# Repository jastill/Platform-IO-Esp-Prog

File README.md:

# PlatformIO ESP32 Debugging

##Platform IO ESP32 Debug Breakout Board

## PCB from [Osh Park](https://oshpark.com)

## Board

Board: [Adafruit Feather 32](https://www.adafruit.com/product/3405)

ESP [Prog Board](https://github.com/espressif/esp-iot-solution/blob/master/documents/evaluation_boards/ESP-Prog_guide_en.md)

## Misc

Step that got ESP-PROG to connect:

Bizarrely it seemed that loading and then unloading these drivers are the change that caused it to work.

https://www.ftdichip.com/Drivers/VCP.htm
sudo kextunload /Library/Extensions/FTDIUSBSerialDriver.kext

### Helpful links to get the port connected

https://docs.platformio.org/en/latest/plus/debug-tools/esp-prog.html

https://community.platformio.org/t/esp-prog-debugging-on-a-mac-no-device-found/14658

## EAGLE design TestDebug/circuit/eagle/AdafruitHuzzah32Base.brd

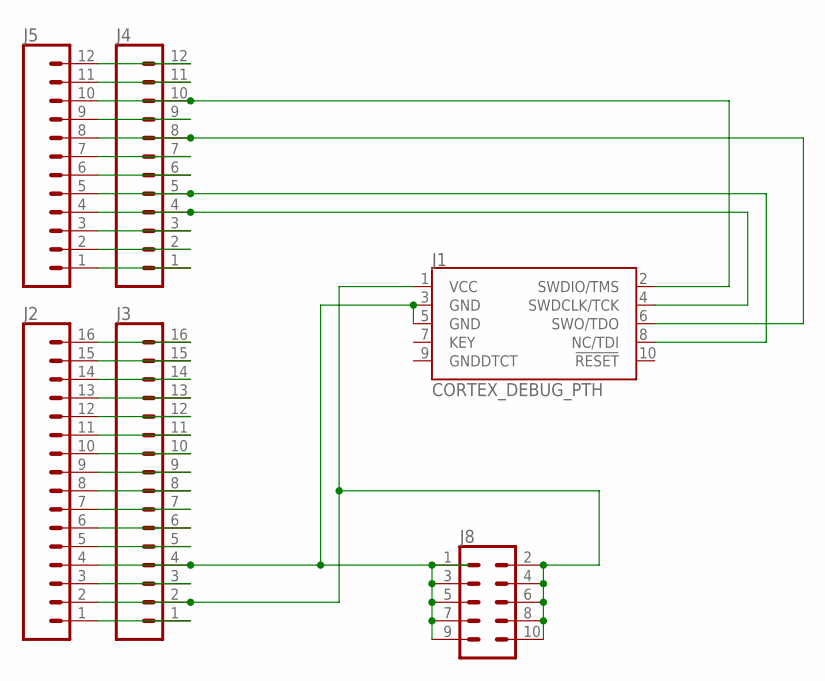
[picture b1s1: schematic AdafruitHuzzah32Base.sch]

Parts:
J1: CORTEX_DEBUG_PTH; 2X5-PTH-1.27MM
J2, J3: CONN_16; 1X16
J4, J5: CONN_12; 1X12
J8: CONN_05X2PTH; 2X5

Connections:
unnamed: J1.1 (VCC), J2.2, J3.2, J8.2, J8.4, J8.6, J8.8, J8.10
unnamed: J1.3 (GND), J1.5 (GND), J2.4, J3.4, J8.1, J8.3, J8.5, J8.7, J8.9
unnamed: J1.6 (SWO/TDO), J4.8, J5.8
unnamed: J1.8 (NC/TDI), J4.5, J5.5
unnamed: J1.4 (SWDCLK/TCK), J4.4, J5.4
unnamed: J1.2 (SWDIO/TMS), J4.10, J5.10
unnamed: J4.12, J5.12
unnamed: J4.11, J5.11
unnamed: J4.9, J5.9
unnamed: J4.7, J5.7
unnamed: J4.6, J5.6
unnamed: J4.3, J5.3
unnamed: J4.2, J5.2
unnamed: J4.1, J5.1
unnamed: J2.16, J3.16
unnamed: J2.15, J3.15
unnamed: J2.14, J3.14
unnamed: J2.13, J3.13
unnamed: J2.12, J3.12
unnamed: J2.11, J3.11
unnamed: J2.10, J3.10
unnamed: J2.9, J3.9
unnamed: J2.8, J3.8
unnamed: J2.7, J3.7
unnamed: J2.6, J3.6
unnamed: J2.5, J3.5
unnamed: J2.3, J3.3
unnamed: J2.1, J3.1

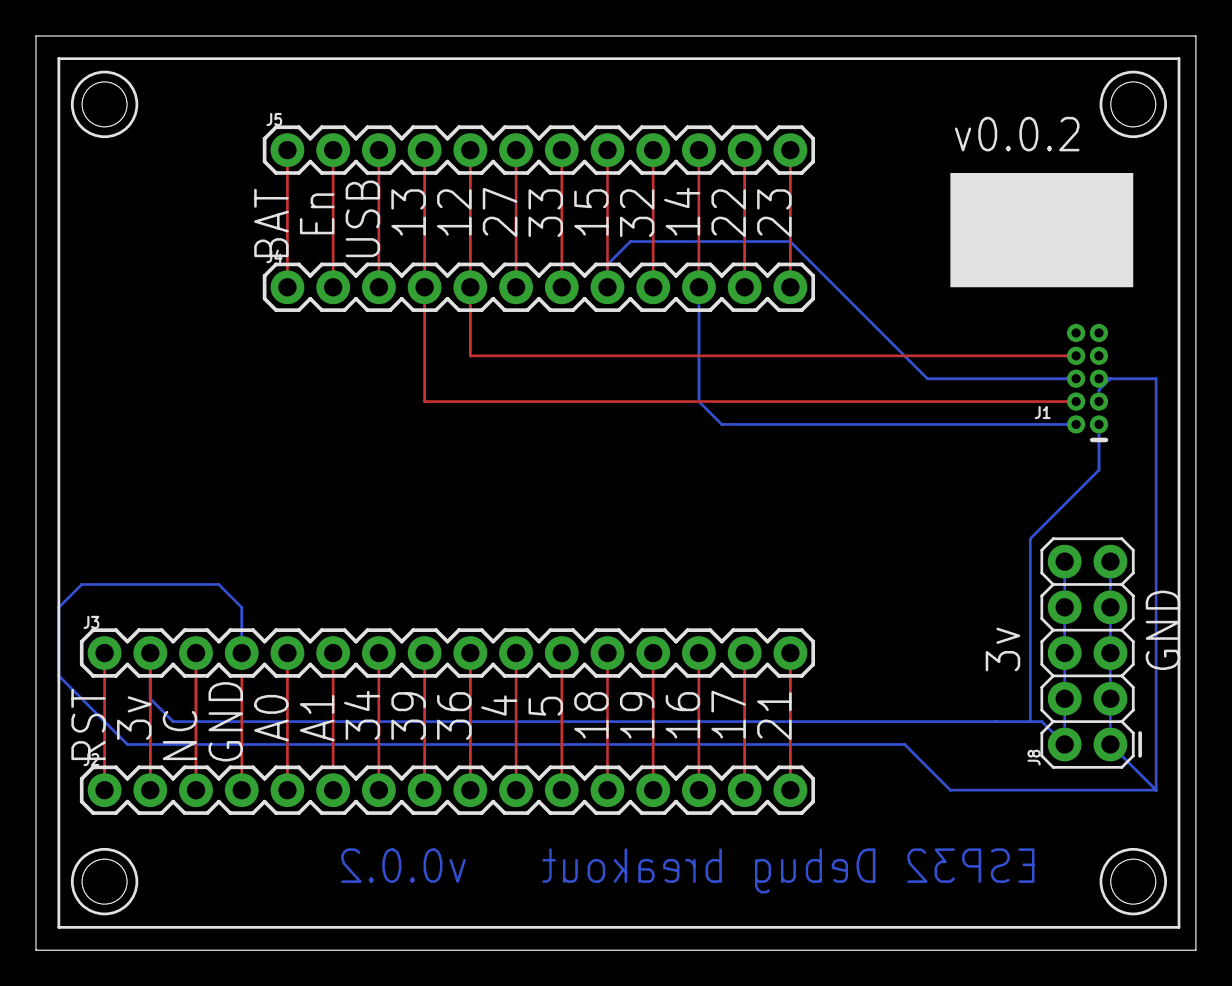
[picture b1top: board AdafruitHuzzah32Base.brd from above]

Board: 2 copper layers, 64.4 x 50.8 mm, 6 parts (0 on the bottom side), 28 nets.

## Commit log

2020-08-22 First version with debugger attaching in Catalina.
2020-08-22 Small docs update
2020-08-22 added fritzing files
2020-08-22 Updated platformio.ini
2020-08-23 Added some simple incrementing code
2020-09-08 Updated profiles to include debg and release for windows
2020-09-09 Added Eagle schematics
2020-09-09 Added power pins and more silk screen
2023-02-03 Added Eagle and fritzing design
2023-02-03 Added ignore
2023-02-03 Added eagle and fritzing
2023-02-03 Added pcb images
2023-02-03 Updated for Osh Park

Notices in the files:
parts and their libraries:
SparkFun-Connectors: Licensing: Creative Commons ShareAlike 4.0 International - https://creativecommons.org/licenses/by-sa/4.0
